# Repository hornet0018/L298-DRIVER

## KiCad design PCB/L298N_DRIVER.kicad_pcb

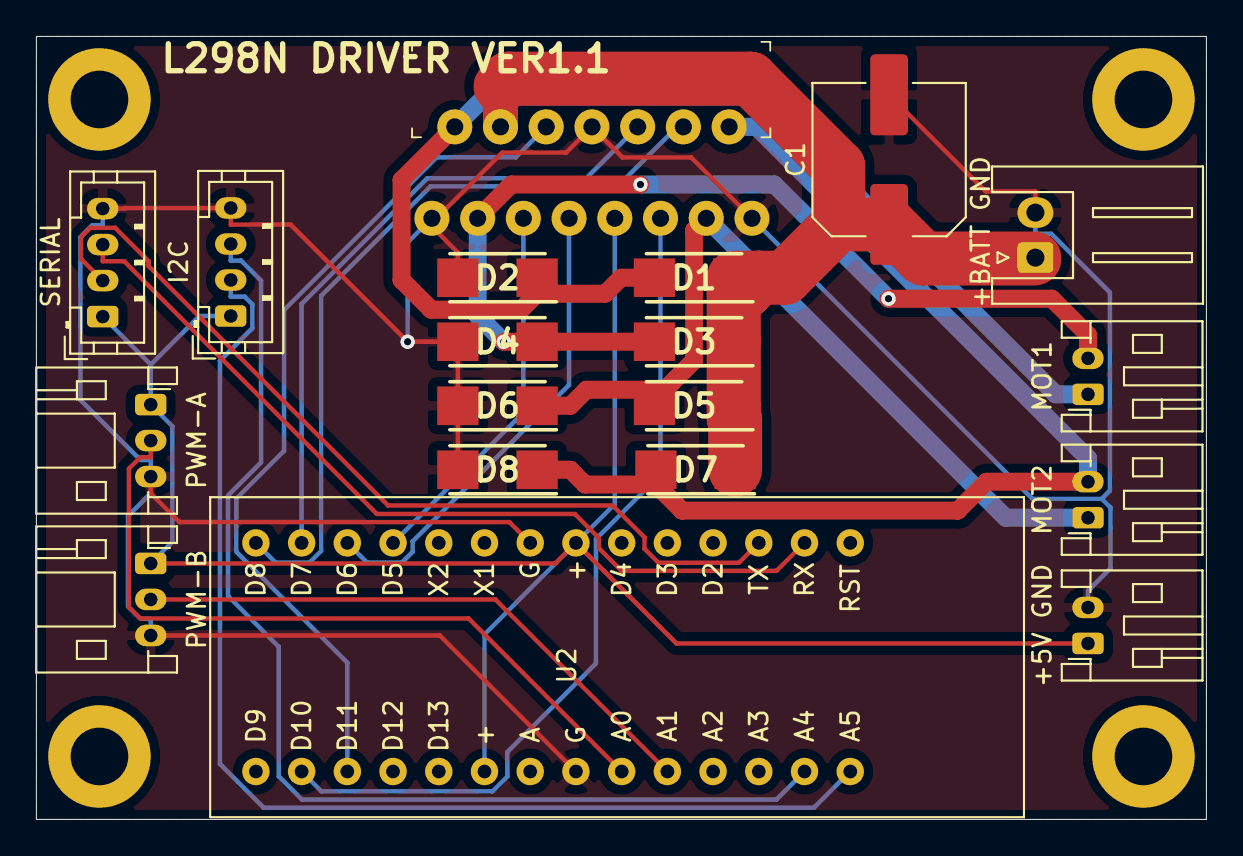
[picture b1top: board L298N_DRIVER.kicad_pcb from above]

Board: 2 copper layers, 65.0 x 43.5 mm, 23 parts (0 on the bottom side), 19 nets.

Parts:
+5V GND: +5V; JST_PH_S2B-PH-K_1x02_P2.00mm_Horizontal
+BATT GND: +BATT; JST_XH_S2B-XH-A_1x02_P2.50mm_Horizontal
C1: C_Small; C_Elec_8x10.2
D1, D2, D3, D4, D5, D6, D7, D8: D_ALT; DIOM5327X242N
H1, H2, H3, H4: MountingHole; MountingHole_3.2mm_M3_ISO7380_Pad
I2C: I2C; JST_PH_B4B-PH-K_1x04_P2.00mm_Vertical
MOT1: MOT1; JST_PH_S2B-PH-K_1x02_P2.00mm_Horizontal
MOT2: MOT02; JST_PH_S2B-PH-K_1x02_P2.00mm_Horizontal
PWM-A: PWM-A; JST_PH_S3B-PH-K_1x03_P2.00mm_Horizontal
PWM-B: PWM-B; JST_PH_S3B-PH-K_1x03_P2.00mm_Horizontal
SERIAL: SERIAL; JST_PH_B4B-PH-K_1x04_P2.00mm_Vertical
U1: L298N; Multiwatt-15
U2: adino2; adino

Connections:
+5V: +5V GND.1, I2C.1, PWM-A.1, PWM-B.1, SERIAL.1, U1.9, U2.7, U2.20
+BATT: +BATT GND.1, C1.1, D1.1, D3.1, D5.1, D7.1, U1.4
/EN_A: U1.6, U2.17
/EN_B: U1.11, U2.16
/IN1: U1.5, U2.11
/IN2: U1.7, U2.12
/IN3: U1.10, U2.13
/IN4: U1.12, U2.14
/OUT1: D1.2, D2.1, MOT1.1, U1.2
/OUT2: D3.2, D4.1, MOT1.2, U1.3
/OUT3: D5.2, D6.1, MOT2.1, U1.13
/OUT4: D7.2, D8.1, MOT2.2, U1.14
/PWM_A: PWM-A.2, U2.23
/PWM_B: PWM-B.2, U2.24
/RX: SERIAL.3, U2.2
/SCL: I2C.2, U2.28
/SDA: I2C.3, U2.27
/TX: SERIAL.2, U2.3
GND: +5V GND.2, +BATT GND.2, C1.2, D2.2, D4.2, D6.2, D8.2, I2C.4, PWM-A.3, PWM-B.3, SERIAL.4, U1.1, U1.8, U1.15, U2.8, U2.22

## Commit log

2020-03-29 pcb update
2020-03-29 v1.1
2020-05-13 bug fix
